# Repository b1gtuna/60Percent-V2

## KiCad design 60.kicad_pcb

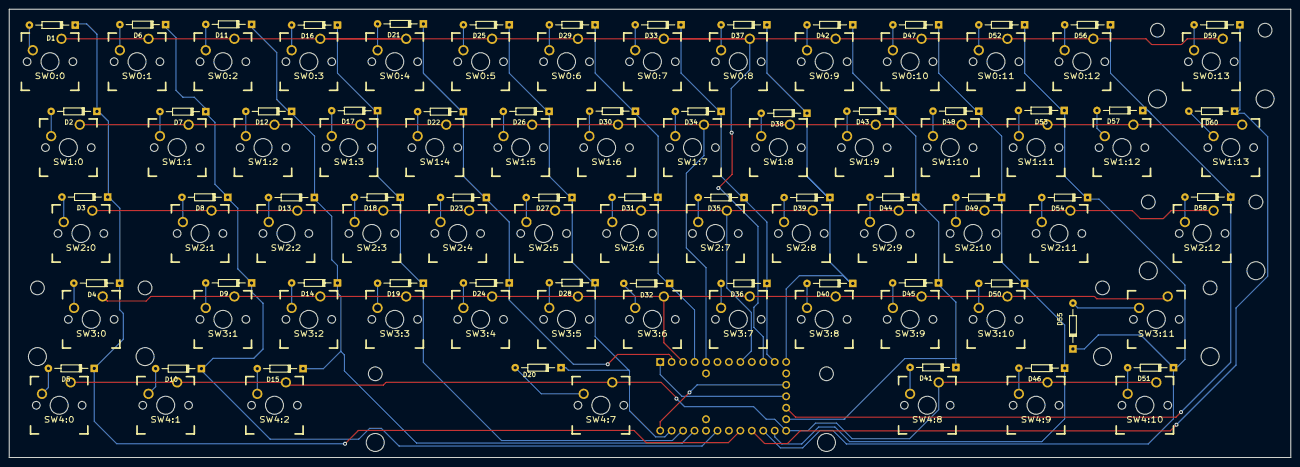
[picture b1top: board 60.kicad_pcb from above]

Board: 2 copper layers, 284.2 x 99.4 mm, 121 parts (1 on the bottom side), 81 nets.

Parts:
D1, D2, D3, D4, D5, D6, D7, D8, D9, D10, D11, D12, D13, D14, D15, D16, D17, D18, D19, D20, D21, D22, D23, D24, D25, D26, D27, D28, D29, D30, D31, D32, D33, D34, D35, D36, D37, D38, D39, D40, D41, D42, D43, D44, D45, D46, D47, D48, D49, D50, D51, D52, D53, D54, D55, D56, D57, D58, D59, D60: DIODE; Diode_DO-35_SOD27_Horizontal_RM10
SW0:0: TILDE; CHERRY_PCB_100H
SW0:1: 1; CHERRY_PCB_100H
SW0:2: 2; CHERRY_PCB_100H
SW0:3: 3; CHERRY_PCB_100H
SW0:4: 4; CHERRY_PCB_100H
SW0:5: 5; CHERRY_PCB_100H
SW0:6: 6; CHERRY_PCB_100H
SW0:7: 7; CHERRY_PCB_100H
SW0:8: 8; CHERRY_PCB_100H
SW0:9: 9; CHERRY_PCB_100H
SW0:10: 10; CHERRY_PCB_100H
SW0:11: -; CHERRY_PCB_100H
SW0:12: =; CHERRY_PCB_100H
SW0:13: BACKSPACE; CHERRY_PCB_200H
SW1:0: TAB; CHERRY_PCB_150H
SW1:1: Q; CHERRY_PCB_100H
SW1:2: W; CHERRY_PCB_100H
SW1:3: E; CHERRY_PCB_100H
SW1:4: R; CHERRY_PCB_100H
SW1:5: T; CHERRY_PCB_100H
SW1:6: Y; CHERRY_PCB_100H
SW1:7: U; CHERRY_PCB_100H
SW1:8: I; CHERRY_PCB_100H
SW1:9: O; CHERRY_PCB_100H
SW1:10: P; CHERRY_PCB_100H
SW1:11: [; CHERRY_PCB_100H
SW1:12: ]; CHERRY_PCB_100H
SW1:13: \; CHERRY_PCB_150H
SW2:0: CAP; CHERRY_PCB_175H
SW2:1: A; CHERRY_PCB_100H
SW2:2: S; CHERRY_PCB_100H
SW2:3: D; CHERRY_PCB_100H
SW2:4: F; CHERRY_PCB_100H
SW2:5: G; CHERRY_PCB_100H
SW2:6: H; CHERRY_PCB_100H
SW2:7: J; CHERRY_PCB_100H
SW2:8: K; CHERRY_PCB_100H
SW2:9: L; CHERRY_PCB_100H
SW2:10: ;; CHERRY_PCB_100H
SW2:11: '; CHERRY_PCB_100H
SW2:12: ENTER; CHERRY_PCB_225H
SW3:0: SHIFT; CHERRY_PCB_200H
SW3:1: Z; CHERRY_PCB_100H
SW3:2: X; CHERRY_PCB_100H
SW3:3: C; CHERRY_PCB_100H
SW3:4: V; CHERRY_PCB_100H
SW3:5: B; CHERRY_PCB_100H
SW3:6: N; CHERRY_PCB_100H
SW3:7: M; CHERRY_PCB_100H
SW3:8: ,; CHERRY_PCB_100H
SW3:9: .; CHERRY_PCB_100H
SW3:10: /; CHERRY_PCB_100H
SW3:11: RIGHT SHIFT; CHERRY_PCB_275H
SW4:0: LEFT_CTRL; CHERRY_PCB_125H
SW4:1: FN; CHERRY_PCB_125H
SW4:2: LEFT_ALT; CHERRY_PCB_125H
SW4:7: SPACE; CHERRY_PCB_625H
SW4:8: RIGHT_ALT; CHERRY_PCB_125H
SW4:9: RIGHT_FN; CHERRY_PCB_125H
SW4:10: RIGHT_CONTROL; CHERRY_PCB_125H
U1: TEENSY2.0; TEENSY_2.0

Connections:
/COL0: D1.2, D2.2, D3.2, D4.2, D5.2, U1.22
/COL1: D6.2, D7.2, D8.2, D9.2, D10.2, U1.24
/COL2: D11.2, D12.2, D13.2, D14.2, D15.2, U1.26
/COL3: D16.2, D17.2, D18.2, D19.2, U1.27
/COL4: D21.2, D22.2, D23.2, D24.2, U1.2
/COL5: D20.2, D25.2, D26.2, D27.2, D28.2, U1.28
/COL6: D29.2, D30.2, D31.2, D32.2, U1.4
/COL7: D33.2, D34.2, D35.2, D36.2, U1.11
/COL8: D37.2, D38.2, D39.2, D40.2, U1.12
/COL9: D41.2, D42.2, D43.2, D44.2, D45.2, U1.17
/COL10: D46.2, D47.2, D48.2, D49.2, D50.2, U1.19
/COL11: D51.2, D52.2, D53.2, D54.2, D55.2, U1.20
/COL12: D56.2, D57.2, D58.2, U1.16
/COL13: D59.2, D60.2, U1.21
/ROW0: SW0:0.1, SW0:1.1, SW0:2.1, SW0:3.1, SW0:4.1, SW0:5.1, SW0:6.1, SW0:7.1, SW0:8.1, SW0:9.1, SW0:10.1, SW0:11.1, SW0:12.1, SW0:13.1, U1.10
/ROW1: SW1:0.1, SW1:1.1, SW1:2.1, SW1:3.1, SW1:4.1, SW1:5.1, SW1:6.1, SW1:7.1, SW1:8.1, SW1:9.1, SW1:10.1, SW1:11.1, SW1:12.1, SW1:13.1, U1.5
/ROW2: SW2:0.1, SW2:1.1, SW2:2.1, SW2:3.1, SW2:4.1, SW2:5.1, SW2:6.1, SW2:7.1, SW2:8.1, SW2:9.1, SW2:10.1, SW2:11.1, SW2:12.1, U1.8
/ROW3: SW3:0.1, SW3:1.1, SW3:2.1, SW3:3.1, SW3:4.1, SW3:5.1, SW3:6.1, SW3:7.1, SW3:8.1, SW3:9.1, SW3:10.1, SW3:11.1, U1.3
/ROW4: SW4:0.1, SW4:1.1, SW4:2.1, SW4:7.1, SW4:8.1, SW4:9.1, SW4:10.1, U1.18
GND: U1.1, U1.15
unnamed: D1.1, SW0:0.2
unnamed: D2.1, SW1:0.2
unnamed: D3.1, SW2:0.2
unnamed: D4.1, SW3:0.2
unnamed: D5.1, SW4:0.2
unnamed: D6.1, SW0:1.2
unnamed: D7.1, SW1:1.2
unnamed: D8.1, SW2:1.2
unnamed: D9.1, SW3:1.2
unnamed: D10.1, SW4:1.2
unnamed: D11.1, SW0:2.2
unnamed: D12.1, SW1:2.2
unnamed: D13.1, SW2:2.2
unnamed: D14.1, SW3:2.2
unnamed: D15.1, SW4:2.2
unnamed: D16.1, SW0:3.2
unnamed: D17.1, SW1:3.2
unnamed: D18.1, SW2:3.2
unnamed: D19.1, SW3:3.2
unnamed: D20.1, SW4:7.2
unnamed: D21.1, SW0:4.2
unnamed: D22.1, SW1:4.2
unnamed: D23.1, SW2:4.2
unnamed: D24.1, SW3:4.2
unnamed: D25.1, SW0:5.2
unnamed: D26.1, SW1:5.2
unnamed: D27.1, SW2:5.2
unnamed: D28.1, SW3:5.2
unnamed: D29.1, SW0:6.2
unnamed: D30.1, SW1:6.2
unnamed: D31.1, SW2:6.2
unnamed: D32.1, SW3:6.2
unnamed: D33.1, SW0:7.2
unnamed: D34.1, SW1:7.2
unnamed: D35.1, SW2:7.2
unnamed: D36.1, SW3:7.2
unnamed: D37.1, SW0:8.2
unnamed: D38.1, SW1:8.2
unnamed: D39.1, SW2:8.2
unnamed: D40.1, SW3:8.2
unnamed: D41.1, SW4:8.2
unnamed: D42.1, SW0:9.2
unnamed: D43.1, SW1:9.2
unnamed: D44.1, SW2:9.2
unnamed: D45.1, SW3:9.2
unnamed: D46.1, SW4:9.2
unnamed: D47.1, SW0:10.2
unnamed: D48.1, SW1:10.2
unnamed: D49.1, SW2:10.2
unnamed: D50.1, SW3:10.2
unnamed: D51.1, SW4:10.2
unnamed: D52.1, SW0:11.2
unnamed: D53.1, SW1:11.2
unnamed: D54.1, SW2:11.2
unnamed: D55.1, SW3:11.2
unnamed: D56.1, SW0:12.2
unnamed: D57.1, SW1:12.2
unnamed: D58.1, SW2:12.2
unnamed: D59.1, SW0:13.2
unnamed: D60.1, SW1:13.2
VCC: U1.14, U1.29

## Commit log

2015-05-18 Merged through hole layers
2015-05-19 Updated for a smaller PCB footprint
